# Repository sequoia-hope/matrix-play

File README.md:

# Matrix Play

Small pocket boards covered in RGB LEDs, made to be played with. Each one is a KiCad design built
around an RP2350A, a LiPo cell and LED matrix drivers. This is a work in progress.

**Project site: <https://sequoia-hope.github.io/matrix-play/>**

The site shows every board family with interactive 3D and layer views, routing status and cost:

- [Board viewer index](https://sequoia-hope.github.io/matrix-play/viewer/index.html)
- [Pattern Explorer](https://sequoia-hope.github.io/matrix-play/design/study/pattern-explorer/):
  LED layout patterns (sunflower, Penrose, Voronoi, halftone, Lissajous) on the round and
  parallelogram outlines

## Board families

| Family | Size | LEDs | Example |
|---|---|---|---|
| Sunflower, 4-layer | Ø 38 mm round | 66–132 XL-1615 | [s2-110](https://sequoia-hope.github.io/matrix-play/viewer/sunflower-s2-110.html) |
| Round pendant | Ø 38 mm round | up to 235 | [round-pendant-e](https://sequoia-hope.github.io/matrix-play/viewer/round-pendant-e.html) |
| Skewed parallelogram, 4-layer | density sweep | 66–264 | [p2-132](https://sequoia-hope.github.io/matrix-play/viewer/parallelogram-p2-132.html) |
| Ultra-dense square | 20 × 20 mm window | 225–256 MHPA0808 | [s16-256](https://sequoia-hope.github.io/matrix-play/viewer/dense-square-s16-256.html) |

## Layout

- `hw/<family>/<variant>/`: KiCad projects
- `design/`: decisions log, status, parts, studies, renders
- `scripts/`: board generators, routing and checking scripts
- `index.html`: the project page (also served locally with `./serve.sh`)
- `vendor/`: pinned pcbview viewer and ultraroute router

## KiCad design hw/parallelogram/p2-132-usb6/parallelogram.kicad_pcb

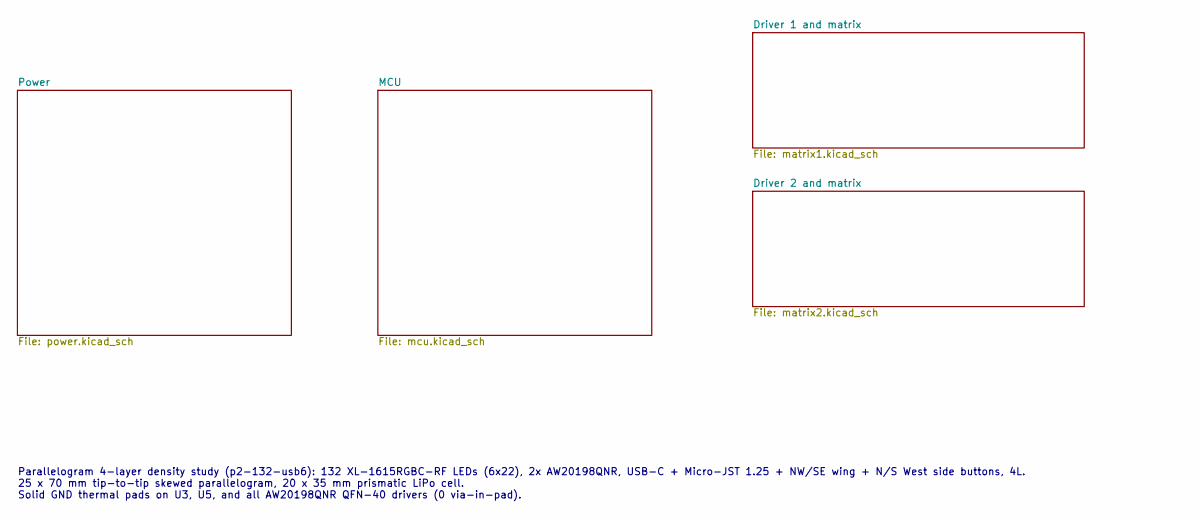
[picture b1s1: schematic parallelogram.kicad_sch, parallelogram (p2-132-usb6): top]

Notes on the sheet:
Parallelogram 4-layer density study (p2-132-usb6): 132 XL-1615RGBC-RF LEDs (6x22), 2x AW20198QNR, USB-C + Micro-JST 1.25 + NW/SE wing + N/S West side buttons, 4L. 25 x 70 mm tip-to-tip skewed parallelogram, 20 x 35 mm prismatic LiPo cell. Solid GND thermal pads on U3, U5, and all AW20198QNR QFN-40 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

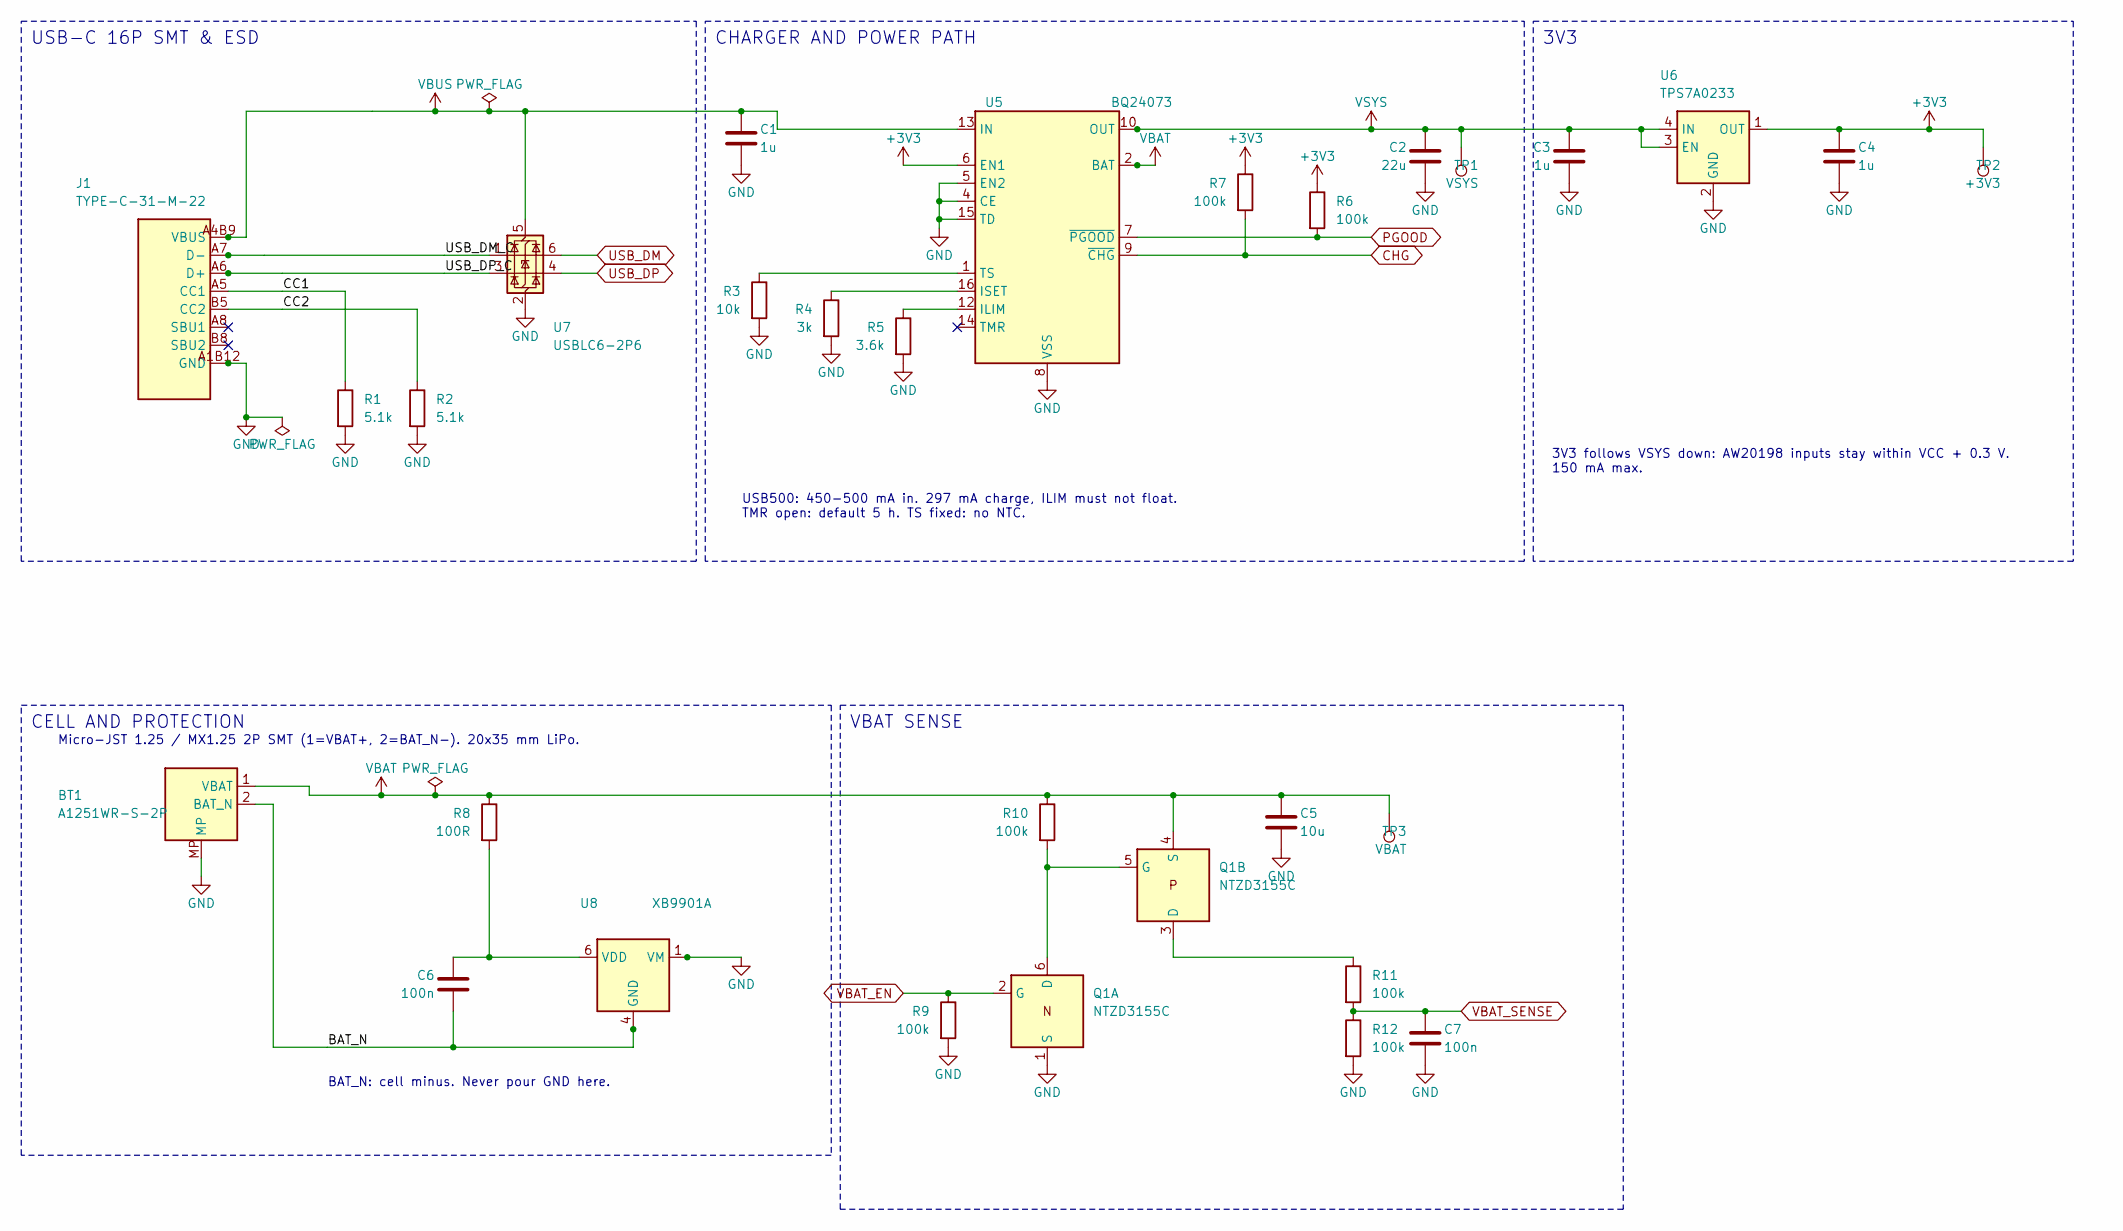
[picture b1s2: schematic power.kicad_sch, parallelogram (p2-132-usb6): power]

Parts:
BT1: A1251WR-S-2P; Molex_PicoBlade_53261-0271_1x02-1MP_P1.25mm_Horizontal; MPN A1251WR-S-2P; LCSC C225111
C1, C3, C4: 1u; C_0402_1005Metric; MPN CL05A105KA5NQNC; LCSC C52923
C2: 22u; C_0603_1608Metric; MPN CL10A226MP8NUNE; LCSC C86295
C5: 10u; C_0603_1608Metric; MPN CL10A106KP8NNNC; LCSC C19702
C6, C7: 100n; C_0402_1005Metric; MPN CL05B104KO5NNNC; LCSC C1525
J1: TYPE-C-31-M-22; USB_C_Receptacle_Hroparts_TYPE-C-31-M-22; MPN TYPE-C-31-M-22; LCSC C530612
Q1: NTZD3155C; SOT-563; MPN NTZD3155CT1G; LCSC C236117
R1, R2: 5.1k; R_0402_1005Metric; MPN 0402WGF5101TCE; LCSC C25905
R3: 10k; R_0402_1005Metric; MPN 0402WGF1002TCE; LCSC C25744
R4: 3k; R_0402_1005Metric; MPN 0402WGF3001TCE; LCSC C25784
R5: 3.6k; R_0402_1005Metric; MPN 0402WGF3601TCE; LCSC C25891
R6, R7, R9, R10, R11, R12: 100k; R_0402_1005Metric; MPN 0402WGF1003TCE; LCSC C25741
R8: 100R; R_0402_1005Metric; MPN 0402WGF1000TCE; LCSC C25076
TP1: VSYS; TestPoint_Pad_D1.0mm
TP2: +3V3; TestPoint_Pad_D1.0mm
TP3: VBAT; TestPoint_Pad_D1.0mm
U5: BQ24073; QFN-16-1EP_3x3mm_P0.5mm_EP1.7x1.7mm; MPN BQ24073RGTR; LCSC C15220
U6: TPS7A0233; Texas_X2SON-4_1x1mm_P0.65mm; MPN TPS7A0233PDQNR; LCSC C2860046
U7: USBLC6-2P6; SOT-666; MPN USBLC6-2P6; LCSC C15999
U8: XB9901A; XySemi_DFN-6_1.8x1.4mm; MPN XB9901A; LCSC C669687

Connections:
+3V3: C4.1, R6.1, R7.1, TP2.1, U5.6 (EN1), U6.1 (OUT); also elsewhere on the board
/Power/BAT_N: BT1.2 (BAT_N), C6.2, U8.4 (GND), U8.5 (GND)
/Power/CC1: J1.A5 (CC1), R1.1
/Power/CC2: J1.B5 (CC2), R2.1
/Power/USB_DM_C: J1.A7 (D-), J1.B7 (D-), U7.1 (I/O1)
/Power/USB_DP_C: J1.A6 (D+), J1.B6 (D+), U7.3 (I/O2)
CHG: R7.2, U5.9 (~CHG); also elsewhere on the board
unnamed: Q1.5 (G), Q1.6 (D), R10.2
unnamed: Q1.3 (D), R11.1
unnamed: R5.1, U5.12 (ILIM)
unnamed: R4.1, U5.16 (ISET)
unnamed: R3.1, U5.1 (TS)
unnamed: C6.1, R8.2, U8.6 (VDD)
PGOOD: R6.2, U5.7 (~PGOOD); also elsewhere on the board
USB_DM: U7.6 (I/O1); also elsewhere on the board
USB_DP: U7.4 (I/O2); also elsewhere on the board
VBAT_EN: Q1.2 (G), R9.1; also elsewhere on the board
VBAT_SENSE: C7.1, R11.2, R12.1; also elsewhere on the board
VSYS: C2.1, C3.1, TP1.1, U5.10 (OUT), U5.11 (OUT), U6.3 (EN), U6.4 (IN); also elsewhere on the board

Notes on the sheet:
USB-C 16P SMT & ESD
USB500: 450-500 mA in. 297 mA charge, ILIM must not float. TMR open: default 5 h. TS fixed: no NTC.
CHARGER AND POWER PATH
3V3 follows VSYS down: AW20198 inputs stay within VCC + 0.3 V. 150 mA max.
3V3
Micro-JST 1.25 / MX1.25 2P SMT (1=VBAT+, 2=BAT_N-). 20x35 mm LiPo.
BAT_N: cell minus. Never pour GND here.
CELL AND PROTECTION
VBAT SENSE

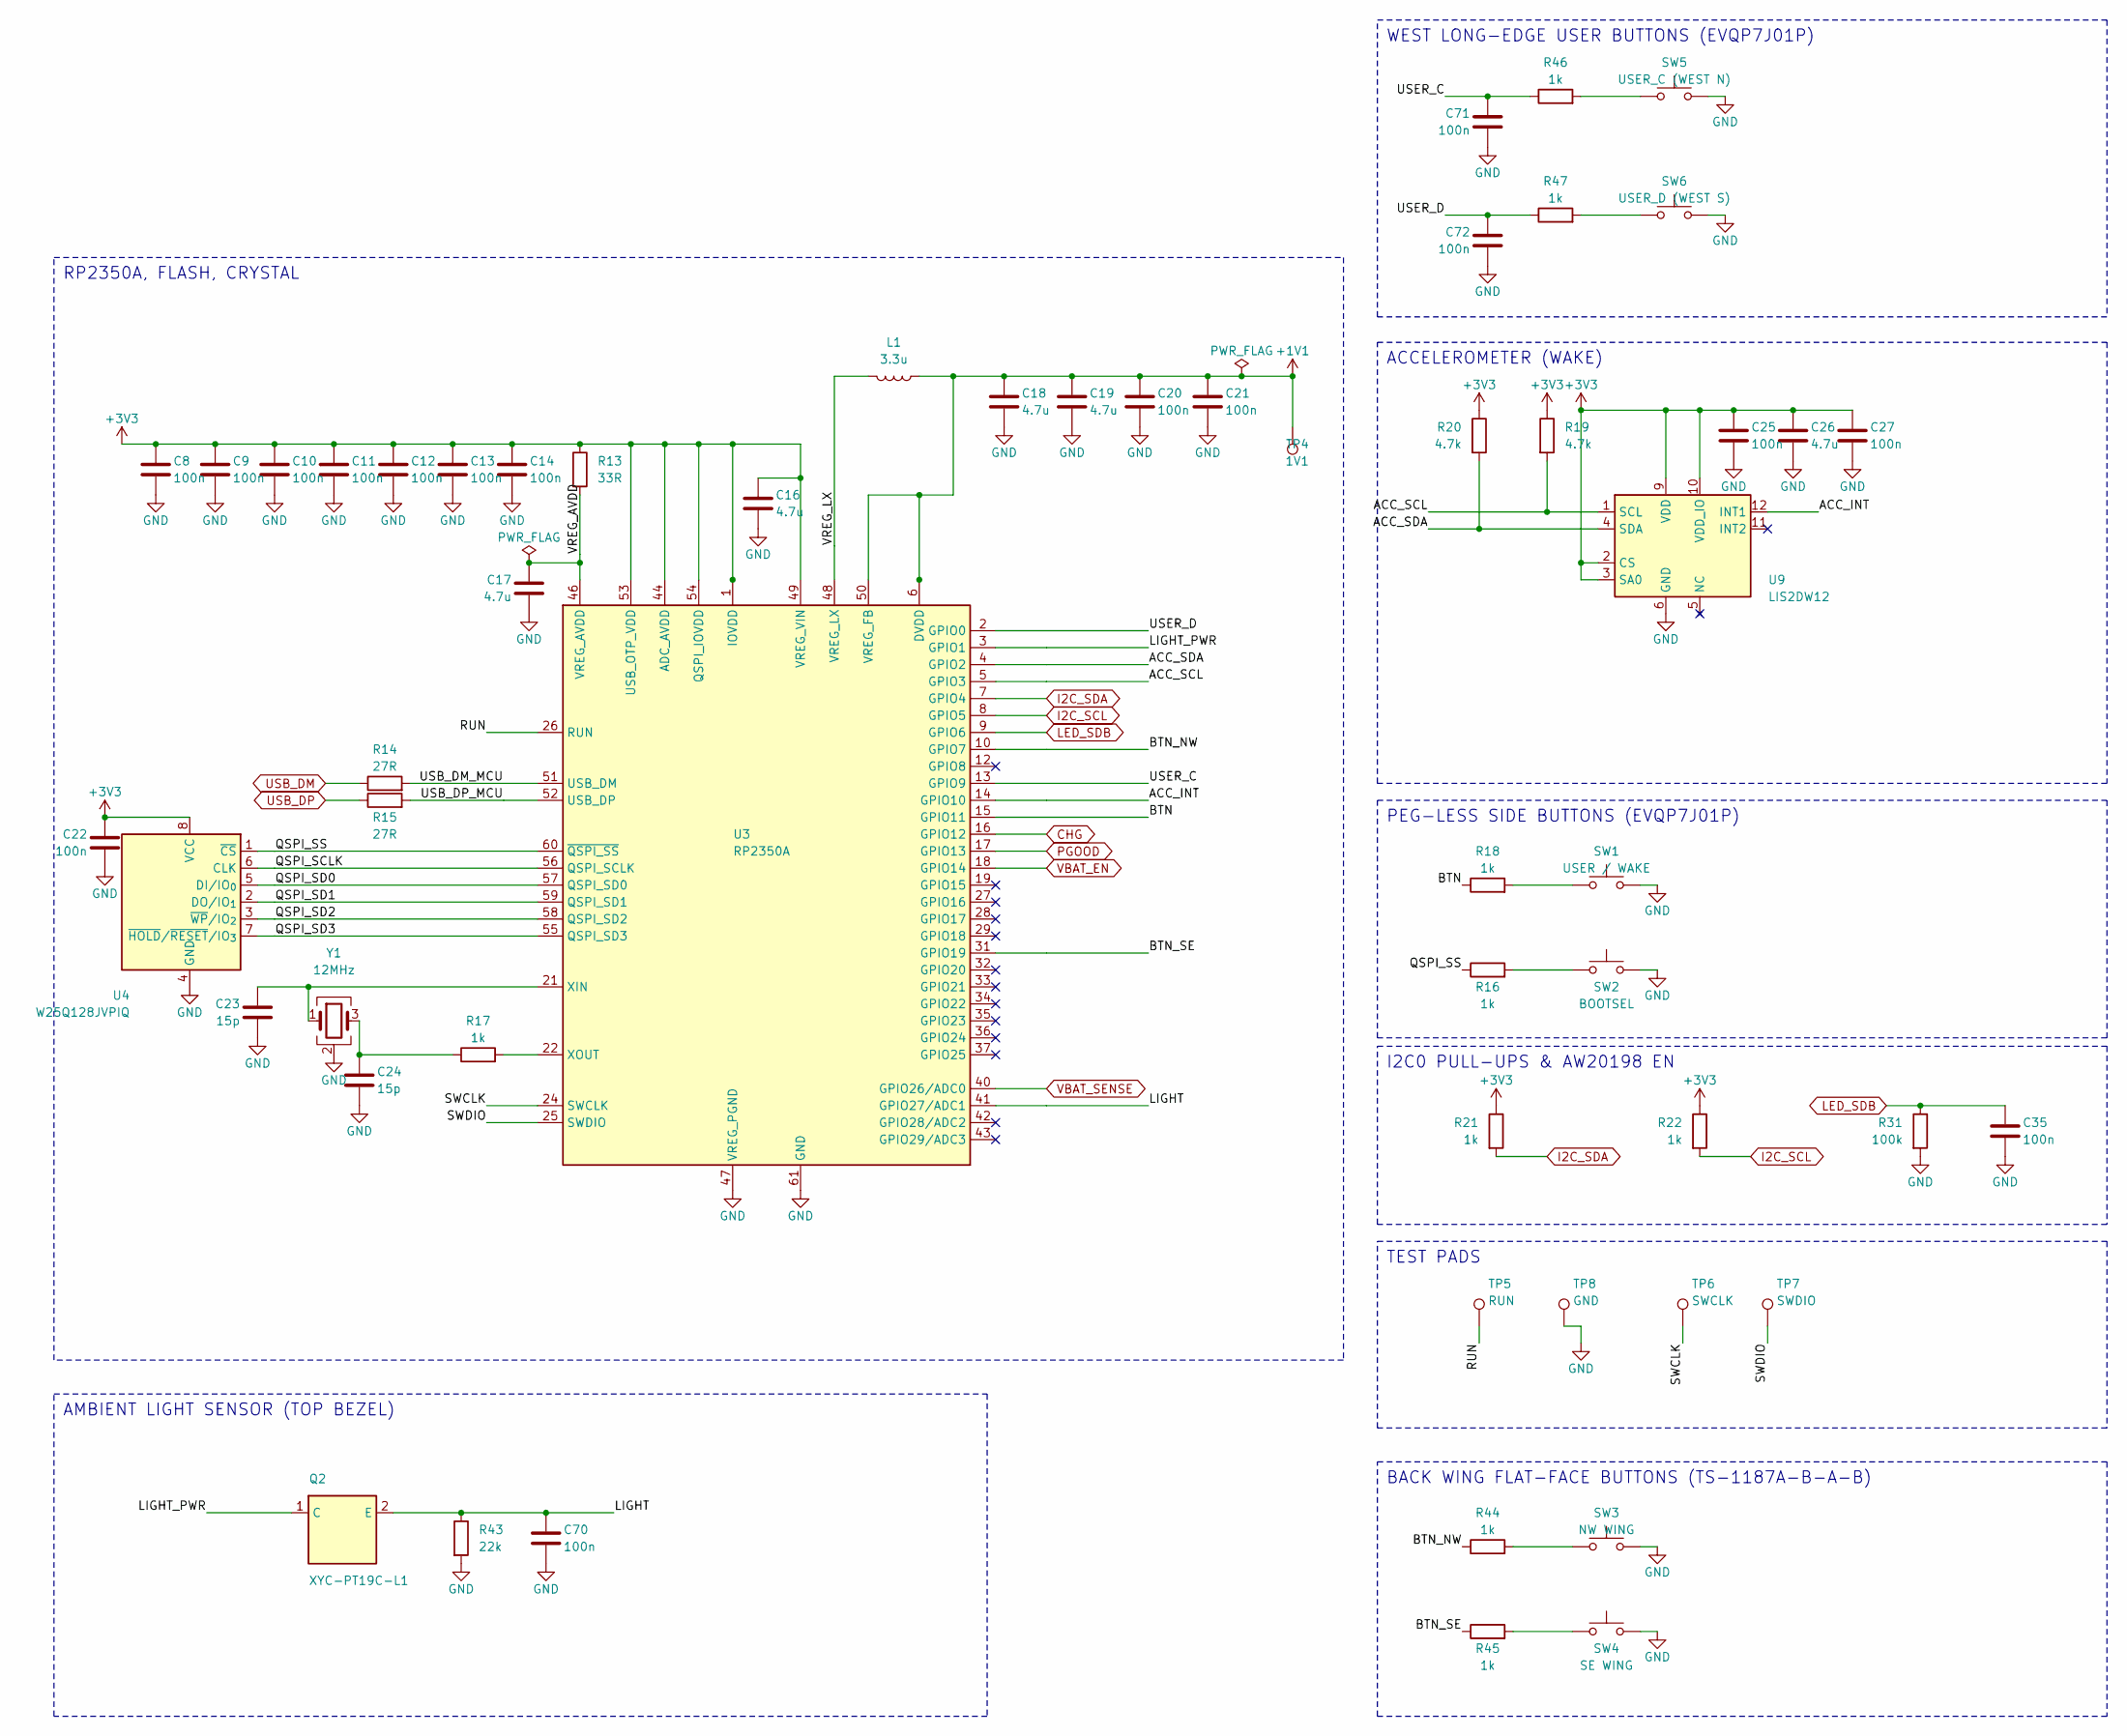
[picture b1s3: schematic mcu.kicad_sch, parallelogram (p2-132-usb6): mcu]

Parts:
C8, C9, C10, C11, C12, C13, C14, C20, C21, C22, C25, C27, C35, C70: 100n; C_0402_1005Metric; MPN CL05B104KO5NNNC; LCSC C1525
C16, C18: 4.7u; C_0402_1005Metric_small_pads; MPN CL05A475MP5NRNC; LCSC C23733
C17, C19, C26: 4.7u; C_0402_1005Metric; MPN CL05A475MP5NRNC; LCSC C23733
C23, C24: 15p; C_0402_1005Metric; MPN 0402CG150J500NT; LCSC C1548
C71, C72: 100n; C_0402_1005Metric; MPN CL05B104KB54PNC; LCSC C307331
L1: 3.3u; L_pol_2016; MPN AOTA-B201610S3R3-101-T; LCSC C42411119
Q2: XYC-PT19C-L1; SENSOR_ALS-PT19; MPN XYC-PT19C-L1; LCSC C2693594
R13: 33R; R_0402_1005Metric; MPN 0402WGF330JTCE; LCSC C25105
R14, R15: 27R; R_0402_1005Metric; MPN 0402WGF270JTCE; LCSC C25100
R16, R17, R18, R21, R22, R44, R45, R46, R47: 1k; R_0402_1005Metric; MPN 0402WGF1001TCE; LCSC C11702
R19, R20: 4.7k; R_0402_1005Metric; MPN 0402WGF4701TCE; LCSC C25900
R31: 100k; R_0402_1005Metric; MPN 0402WGF1003TCE; LCSC C25741
R43: 22k; R_0402_1005Metric; MPN 0402WGF2202TCE; LCSC C25768
SW1: USER / WAKE; SW_Panasonic_EVQP7J; MPN EVQP7J01P; LCSC C2828254
SW2: BOOTSEL; SW_Panasonic_EVQP7J; MPN EVQP7J01P; LCSC C2828254
SW3: NW WING; SW_Push_1P1T_XKB_TS-1187A; MPN TS-1187A-B-A-B; LCSC C318884
SW4: SE WING; SW_Push_1P1T_XKB_TS-1187A; MPN TS-1187A-B-A-B; LCSC C318884
SW5: USER_C (WEST N); SW_Panasonic_EVQP7J; MPN EVQP7J01P; LCSC C2828254
SW6: USER_D (WEST S); SW_Panasonic_EVQP7J; MPN EVQP7J01P; LCSC C2828254
TP4: 1V1; TestPoint_Pad_D1.0mm
TP5: RUN; TestPoint_Pad_D1.0mm
TP6: SWCLK; TestPoint_Pad_D1.0mm
TP7: SWDIO; TestPoint_Pad_D1.0mm
TP8: GND; TestPoint_Pad_D1.0mm
U3: RP2350A; RP2350-QFN-60-1EP_7x7_P0.4mm_EP3.4x3.4mm_ThermalVias; MPN RP2350A; LCSC C42411118
U4: W25Q128JVPIQ; WSON-8_6x5mm_P1.27mm_NoEPCopper; MPN W25Q128JVPIQ; LCSC C190862
U9: LIS2DW12; LGA-12_2x2mm_P0.5mm; MPN LIS2DW12TR; LCSC C189624
Y1: 12MHz; Crystal_SMD_3225-4Pin_3.2x2.5mm; MPN ABM8-272-T3; LCSC C20625731

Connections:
+3V3: C8.1, C9.1, C10.1, C11.1, C12.1, C13.1, C14.1, C16.1, C22.1, C25.1, C26.1, C27.1, R13.1, R19.1, R20.1, R21.1, R22.1, U3.1 (IOVDD), U3.11 (IOVDD), U3.20 (IOVDD), U3.30 (IOVDD), U3.38 (IOVDD), U3.44 (ADC_AVDD), U3.45 (IOVDD), U3.49 (VREG_VIN), U3.53 (USB_OTP_VDD), U3.54 (QSPI_IOVDD), U4.8 (VCC), U9.2 (CS), U9.3 (SA0), U9.9 (VDD), U9.10 (VDD_IO); also elsewhere on the board
/MCU/ACC_INT: U3.14 (GPIO10), U9.12 (INT1)
/MCU/ACC_SCL: R19.2, U3.5 (GPIO3), U9.1 (SCL)
/MCU/ACC_SDA: R20.2, U3.4 (GPIO2), U9.4 (SDA)
/MCU/BTN: R18.1, U3.15 (GPIO11)
/MCU/BTN_NW: R44.1, U3.10 (GPIO7)
/MCU/BTN_SE: R45.1, U3.31 (GPIO19)
/MCU/LIGHT: C70.1, Q2.2 (E), R43.1, U3.41 (GPIO27/ADC1)
/MCU/LIGHT_PWR: Q2.1 (C), U3.3 (GPIO1)
/MCU/QSPI_SCLK: U3.56 (QSPI_SCLK), U4.6 (CLK)
/MCU/QSPI_SD0: U3.57 (QSPI_SD0), U4.5 (DI/IO_{0})
/MCU/QSPI_SD1: U3.59 (QSPI_SD1), U4.2 (DO/IO_{1})
/MCU/QSPI_SD2: U3.58 (QSPI_SD2), U4.3 (~WP/IO_{2})
/MCU/QSPI_SD3: U3.55 (QSPI_SD3), U4.7 (~HOLD/~RESET/IO_{3})
/MCU/QSPI_SS: R16.1, U3.60 (~QSPI_SS), U4.1 (~CS)
/MCU/RUN: TP5.1, U3.26 (RUN)
/MCU/SWCLK: TP6.1, U3.24 (SWCLK)
/MCU/SWDIO: TP7.1, U3.25 (SWDIO)
/MCU/USB_DM_MCU: R14.2, U3.51 (USB_DM)
/MCU/USB_DP_MCU: R15.2, U3.52 (USB_DP)
/MCU/USER_C: C71.1, R46.1, U3.13 (GPIO9)
/MCU/USER_D: C72.1, R47.1, U3.2 (GPIO0)
/MCU/VREG_LX: L1.2, U3.48 (VREG_LX)
CHG: U3.16 (GPIO12); also elsewhere on the board
I2C_SCL: R22.2, U3.8 (GPIO5); also elsewhere on the board
I2C_SDA: R21.2, U3.7 (GPIO4); also elsewhere on the board
LED_SDB: C35.1, R31.1, U3.9 (GPIO6); also elsewhere on the board
unnamed: C24.1, R17.1, Y1.3
unnamed: R16.2, SW2.1
unnamed: R18.2, SW1.1
unnamed: R44.2, SW3.1
unnamed: R45.2, SW4.1
unnamed: R46.2, SW5.1
unnamed: R47.2, SW6.1
unnamed: C23.1, U3.21 (XIN), Y1.1
unnamed: R17.2, U3.22 (XOUT)
PGOOD: U3.17 (GPIO13); also elsewhere on the board
USB_DM: R14.1; also elsewhere on the board
USB_DP: R15.1; also elsewhere on the board
VBAT_EN: U3.18 (GPIO14); also elsewhere on the board
VBAT_SENSE: U3.40 (GPIO26/ADC0); also elsewhere on the board

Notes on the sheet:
RP2350A, FLASH, CRYSTAL
ACCELEROMETER (WAKE)
PEG-LESS SIDE BUTTONS (EVQP7J01P)
I2C0 PULL-UPS & AW20198 EN
TEST PADS
AMBIENT LIGHT SENSOR (TOP BEZEL)
BACK WING FLAT-FACE BUTTONS (TS-1187A-B-A-B)
WEST LONG-EDGE USER BUTTONS (EVQP7J01P)

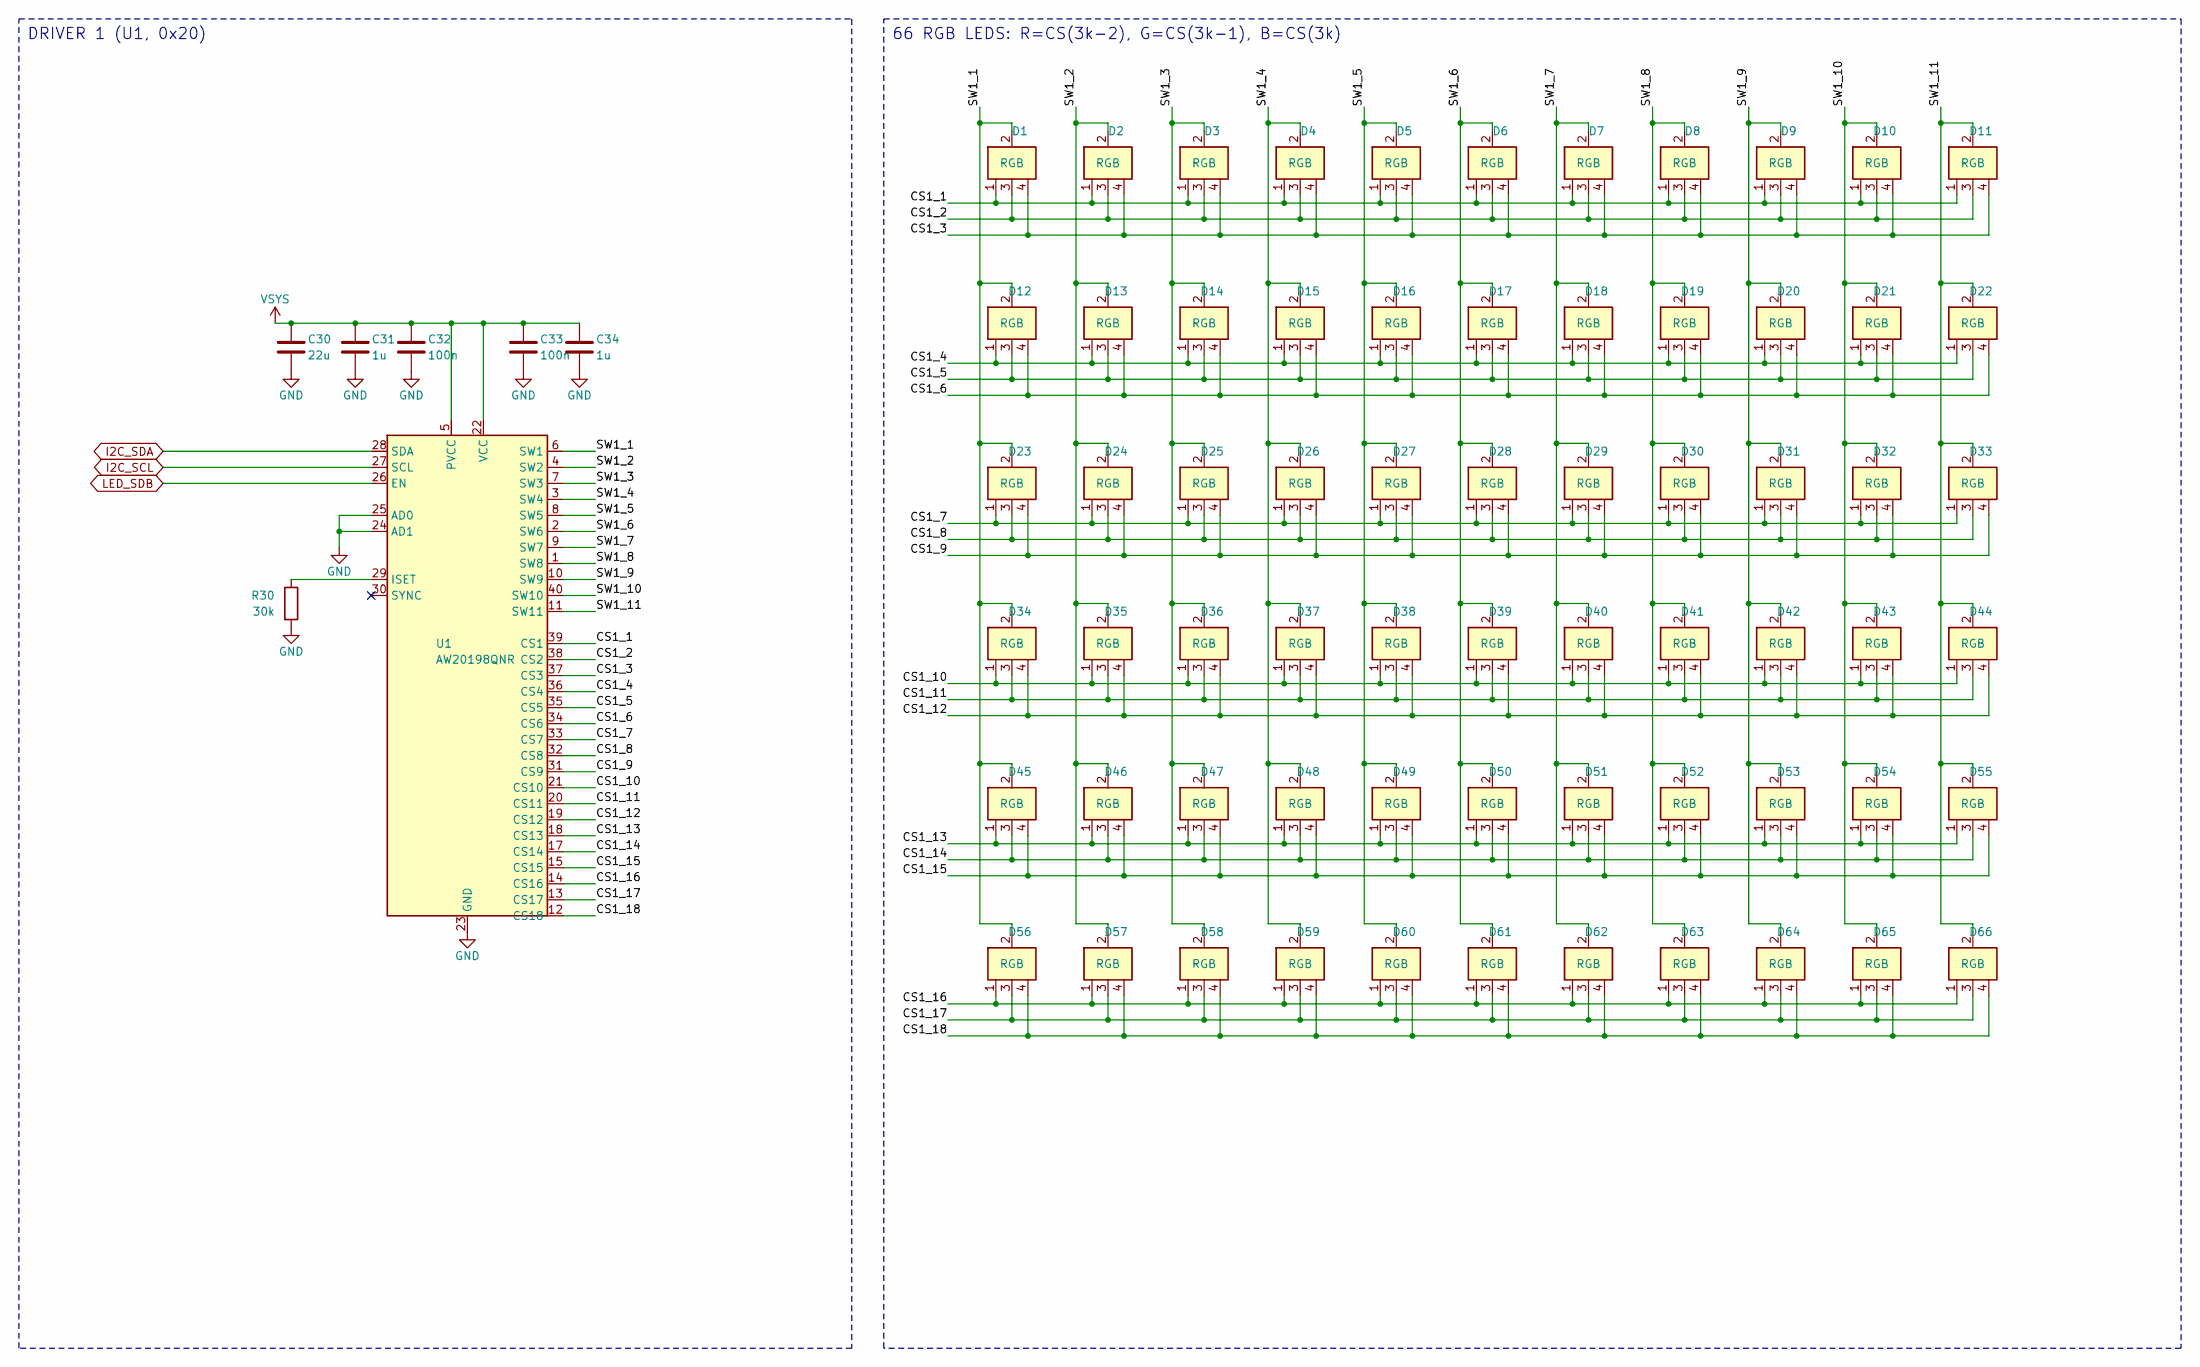
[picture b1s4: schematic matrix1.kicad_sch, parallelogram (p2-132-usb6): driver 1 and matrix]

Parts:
C30: 22u; C_0603_1608Metric; MPN CL10A226MP8NUNE; LCSC C86295
C31, C34: 1u; C_0402_1005Metric; MPN CL05A105KA5NQNC; LCSC C52923
C32, C33: 100n; C_0402_1005Metric; MPN CL05B104KO5NNNC; LCSC C1525
D1, D2, D3, D4, D5, D6, D7, D8, D9, D10, D11, D12, D13, D14, D15, D16, D17, D18, D19, D20, D21, D22, D23, D24, D25, D26, D27, D28, D29, D30, D31, D32, D33, D34, D35, D36, D37, D38, D39, D40, D41, D42, D43, D44, D45, D46, D47, D48, D49, D50, D51, D52, D53, D54, D55, D56, D57, D58, D59, D60, D61, D62, D63, D64, D65, D66: RGB; LED_XL-1615RGBC; MPN XL-1615RGBC-RF; LCSC C965840
R30: 30k; R_0402_1005Metric; MPN 0402WGF3002TCE; LCSC C25776
U1: AW20198QNR; AW20198_QFN-40-1EP_5x5mm_P0.4mm_EP3.4x3.4mm; MPN AW20198QNR; LCSC C5137654

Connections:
/Driver 1 and matrix/CS1_1: D1.1 (R), D2.1 (R), D3.1 (R), D4.1 (R), D5.1 (R), D6.1 (R), D7.1 (R), D8.1 (R), D9.1 (R), D10.1 (R), D11.1 (R), U1.39 (CS1)
/Driver 1 and matrix/CS1_2: D1.3 (G), D2.3 (G), D3.3 (G), D4.3 (G), D5.3 (G), D6.3 (G), D7.3 (G), D8.3 (G), D9.3 (G), D10.3 (G), D11.3 (G), U1.38 (CS2)
/Driver 1 and matrix/CS1_3: D1.4 (B), D2.4 (B), D3.4 (B), D4.4 (B), D5.4 (B), D6.4 (B), D7.4 (B), D8.4 (B), D9.4 (B), D10.4 (B), D11.4 (B), U1.37 (CS3)
/Driver 1 and matrix/CS1_4: D12.1 (R), D13.1 (R), D14.1 (R), D15.1 (R), D16.1 (R), D17.1 (R), D18.1 (R), D19.1 (R), D20.1 (R), D21.1 (R), D22.1 (R), U1.36 (CS4)
/Driver 1 and matrix/CS1_5: D12.3 (G), D13.3 (G), D14.3 (G), D15.3 (G), D16.3 (G), D17.3 (G), D18.3 (G), D19.3 (G), D20.3 (G), D21.3 (G), D22.3 (G), U1.35 (CS5)
/Driver 1 and matrix/CS1_6: D12.4 (B), D13.4 (B), D14.4 (B), D15.4 (B), D16.4 (B), D17.4 (B), D18.4 (B), D19.4 (B), D20.4 (B), D21.4 (B), D22.4 (B), U1.34 (CS6)
/Driver 1 and matrix/CS1_7: D23.1 (R), D24.1 (R), D25.1 (R), D26.1 (R), D27.1 (R), D28.1 (R), D29.1 (R), D30.1 (R), D31.1 (R), D32.1 (R), D33.1 (R), U1.33 (CS7)
/Driver 1 and matrix/CS1_8: D23.3 (G), D24.3 (G), D25.3 (G), D26.3 (G), D27.3 (G), D28.3 (G), D29.3 (G), D30.3 (G), D31.3 (G), D32.3 (G), D33.3 (G), U1.32 (CS8)
/Driver 1 and matrix/CS1_9: D23.4 (B), D24.4 (B), D25.4 (B), D26.4 (B), D27.4 (B), D28.4 (B), D29.4 (B), D30.4 (B), D31.4 (B), D32.4 (B), D33.4 (B), U1.31 (CS9)
/Driver 1 and matrix/CS1_10: D34.1 (R), D35.1 (R), D36.1 (R), D37.1 (R), D38.1 (R), D39.1 (R), D40.1 (R), D41.1 (R), D42.1 (R), D43.1 (R), D44.1 (R), U1.21 (CS10)
/Driver 1 and matrix/CS1_11: D34.3 (G), D35.3 (G), D36.3 (G), D37.3 (G), D38.3 (G), D39.3 (G), D40.3 (G), D41.3 (G), D42.3 (G), D43.3 (G), D44.3 (G), U1.20 (CS11)
/Driver 1 and matrix/CS1_12: D34.4 (B), D35.4 (B), D36.4 (B), D37.4 (B), D38.4 (B), D39.4 (B), D40.4 (B), D41.4 (B), D42.4 (B), D43.4 (B), D44.4 (B), U1.19 (CS12)
/Driver 1 and matrix/CS1_13: D45.1 (R), D46.1 (R), D47.1 (R), D48.1 (R), D49.1 (R), D50.1 (R), D51.1 (R), D52.1 (R), D53.1 (R), D54.1 (R), D55.1 (R), U1.18 (CS13)
/Driver 1 and matrix/CS1_14: D45.3 (G), D46.3 (G), D47.3 (G), D48.3 (G), D49.3 (G), D50.3 (G), D51.3 (G), D52.3 (G), D53.3 (G), D54.3 (G), D55.3 (G), U1.17 (CS14)
/Driver 1 and matrix/CS1_15: D45.4 (B), D46.4 (B), D47.4 (B), D48.4 (B), D49.4 (B), D50.4 (B), D51.4 (B), D52.4 (B), D53.4 (B), D54.4 (B), D55.4 (B), U1.15 (CS15)
/Driver 1 and matrix/CS1_16: D56.1 (R), D57.1 (R), D58.1 (R), D59.1 (R), D60.1 (R), D61.1 (R), D62.1 (R), D63.1 (R), D64.1 (R), D65.1 (R), D66.1 (R), U1.14 (CS16)
/Driver 1 and matrix/CS1_17: D56.3 (G), D57.3 (G), D58.3 (G), D59.3 (G), D60.3 (G), D61.3 (G), D62.3 (G), D63.3 (G), D64.3 (G), D65.3 (G), D66.3 (G), U1.13 (CS17)
/Driver 1 and matrix/CS1_18: D56.4 (B), D57.4 (B), D58.4 (B), D59.4 (B), D60.4 (B), D61.4 (B), D62.4 (B), D63.4 (B), D64.4 (B), D65.4 (B), D66.4 (B), U1.12 (CS18)
/Driver 1 and matrix/SW1_1: D1.2 (A), D12.2 (A), D23.2 (A), D34.2 (A), D45.2 (A), D56.2 (A), U1.6 (SW1)
/Driver 1 and matrix/SW1_2: D2.2 (A), D13.2 (A), D24.2 (A), D35.2 (A), D46.2 (A), D57.2 (A), U1.4 (SW2)
/Driver 1 and matrix/SW1_3: D3.2 (A), D14.2 (A), D25.2 (A), D36.2 (A), D47.2 (A), D58.2 (A), U1.7 (SW3)
/Driver 1 and matrix/SW1_4: D4.2 (A), D15.2 (A), D26.2 (A), D37.2 (A), D48.2 (A), D59.2 (A), U1.3 (SW4)
/Driver 1 and matrix/SW1_5: D5.2 (A), D16.2 (A), D27.2 (A), D38.2 (A), D49.2 (A), D60.2 (A), U1.8 (SW5)
/Driver 1 and matrix/SW1_6: D6.2 (A), D17.2 (A), D28.2 (A), D39.2 (A), D50.2 (A), D61.2 (A), U1.2 (SW6)
/Driver 1 and matrix/SW1_7: D7.2 (A), D18.2 (A), D29.2 (A), D40.2 (A), D51.2 (A), D62.2 (A), U1.9 (SW7)
/Driver 1 and matrix/SW1_8: D8.2 (A), D19.2 (A), D30.2 (A), D41.2 (A), D52.2 (A), D63.2 (A), U1.1 (SW8)
/Driver 1 and matrix/SW1_9: D9.2 (A), D20.2 (A), D31.2 (A), D42.2 (A), D53.2 (A), D64.2 (A), U1.10 (SW9)
/Driver 1 and matrix/SW1_10: D10.2 (A), D21.2 (A), D32.2 (A), D43.2 (A), D54.2 (A), D65.2 (A), U1.40 (SW10)
/Driver 1 and matrix/SW1_11: D11.2 (A), D22.2 (A), D33.2 (A), D44.2 (A), D55.2 (A), D66.2 (A), U1.11 (SW11)
I2C_SCL: U1.27 (SCL); also elsewhere on the board
I2C_SDA: U1.28 (SDA); also elsewhere on the board
LED_SDB: U1.26 (EN); also elsewhere on the board
unnamed: R30.1, U1.29 (ISET)
VSYS: C30.1, C31.1, C32.1, C33.1, C34.1, U1.5 (PVCC), U1.22 (VCC); also elsewhere on the board

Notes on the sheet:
DRIVER 1 (U1, 0x20)
66 RGB LEDS: R=CS(3k-2), G=CS(3k-1), B=CS(3k)

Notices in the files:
hw/parallelogram/p1-66-usb/matrix1.kicad_sch:
CERN-OHL-P-2.0
hw/parallelogram/p2-132-usb6/parallelogram.kicad_pcb:
CERN-OHL-P
scripts/schematic.py:
company="CERN-OHL-P-2.0", comments=[comment, "Drawn by scripts/schematic.py"],
